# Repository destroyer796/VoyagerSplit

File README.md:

# VoyagerSplit
A wireless low profile keyboard made for [Hack Club](https://hackclub.com/)'s [Blueprint](https://blueprint.hackclub.com/) program. It uses a staggered columnar layout with 28 keys on each side, with 4 thumb buttons. It uses Kailh Choc switches and Seeed Studio Xiao BLE microcontrollers.

## Why?
I decided to design this keyboard to help improve my typing speed and to give me a mechanical keyboard option for when I'm travelling or away from my PC, as I go into college. I wanted to keep it fairly similar to a conventional keyboard though to prevent too much learning curve.

## Renders

## PCB

## Schematic

## BOM
|Item                |Description    |Quantity|Total Price(with shipping)|URL                                                                                                                                                                                                                                                                                                                                                                                                                                                                                                                                                                                                                                                                                                                                                                                 |
|--------------------|---------------|--------|--------------------------|------------------------------------------------------------------------------------------------------------------------------------------------------------------------------------------------------------------------------------------------------------------------------------------------------------------------------------------------------------------------------------------------------------------------------------------------------------------------------------------------------------------------------------------------------------------------------------------------------------------------------------------------------------------------------------------------------------------------------------------------------------------------------------|
|Xiao nRF52840       |Microcontroller|2       |40.06                     |https://www.aliexpress.us/item/3256804273304037.html?spm=a2g0o.productlist.main.17.1d7f5aLD5aLDFO&algo_pvid=72d61333-23ef-4914-a85a-eb0545dd1005&algo_exp_id=72d61333-23ef-4914-a85a-eb0545dd1005-16&pdp_ext_f=%7B%22order%22%3A%22285%22%2C%22eval%22%3A%221%22%2C%22fromPage%22%3A%22search%22%7D&pdp_npi=6%40dis%21USD%2171.90%2153.92%21%21%2171.90%2153.92%21%402101e2b617649016405177918e3363%2112000038983356071%21sea%21US%212965353747%21X%211%210%21n_tag%3A-29919%3Bd%3Add1f422%3Bm03_new_user%3A-29895&curPageLogUid=hr13WqN6qxqv&utparam-url=scene%3Asearch%7Cquery_from%3A%7Cx_object_id%3A1005004459618789%7C_p_origin_prod%3A                                                                                                                                       |
|1N5819 SOD123 Diodes|Diodes         |56      |0.99                      |https://www.aliexpress.us/item/3256801808479789.html?spm=a2g0o.productlist.main.2.5cfb3tgy3tgyW8&algo_pvid=5502a66d-f71d-47d2-b8b7-ee42b102c6e6&algo_exp_id=5502a66d-f71d-47d2-b8b7-ee42b102c6e6-1&pdp_ext_f=%7B%22order%22%3A%22144%22%2C%22eval%22%3A%221%22%2C%22fromPage%22%3A%22search%22%7D&pdp_npi=6%40dis%21USD%211.38%210.99%21%21%211.38%210.99%21%40210337c117649020322812544ee2f6%2112000018351925967%21sea%21US%212965353747%21X%211%210%21n_tag%3A-29919%3Bd%3Add1f422%3Bm03_new_user%3A-29895%3BpisId%3A5000000191712753&curPageLogUid=OMce55HFjq8i&utparam-url=scene%3Asearch%7Cquery_from%3A%7Cx_object_id%3A1005001994794541%7C_p_origin_prod%3A                                                                                                                  |
|Kailh Choc Reds     |Switches       |56      |30.83                     |https://www.aliexpress.us/item/3256808620484354.html?spm=a2g0o.productlist.main.3.39ac194b9vLyR5&algo_pvid=734049b5-ba85-4d7e-95c6-9e496b0393b3&algo_exp_id=734049b5-ba85-4d7e-95c6-9e496b0393b3-2&pdp_ext_f=%7B%22order%22%3A%22189%22%2C%22eval%22%3A%221%22%2C%22fromPage%22%3A%22search%22%7D&pdp_npi=6%40dis%21USD%2130.83%2124.33%21%21%2130.83%2124.33%21%402101e8f317649021499408071e3116%2112000046742202221%21sea%21US%212965353747%21X%211%210%21n_tag%3A-29919%3Bd%3Add1f422%3Bm03_new_user%3A-29895%3BpisId%3A5000000191712753&curPageLogUid=ucF7cwdLXpYV&utparam-url=scene%3Asearch%7Cquery_from%3A%7Cx_object_id%3A1005008806799106%7C_p_origin_prod%3A                                                                                                              |
|Lipo Battery        |140 mAh 302025 |2       |5.51                      |https://www.aliexpress.us/item/3256808031709894.html?spm=a2g0o.productlist.main.4.4571BRfbBRfbo4&aem_p4p_detail=202512041858096342662010559000000555021&algo_pvid=34977370-c03c-490e-b3f1-619f2c1c78e8&algo_exp_id=34977370-c03c-490e-b3f1-619f2c1c78e8-3&pdp_ext_f=%7B%22order%22%3A%222831%22%2C%22eval%22%3A%221%22%2C%22fromPage%22%3A%22search%22%7D&pdp_npi=6%40dis%21USD%2112.25%210.99%21%21%2186.12%216.99%21%40210319b017649034893272527e3fea%2112000044269020516%21sea%21US%212965353747%21X%211%210%21n_tag%3A-29919%3Bd%3Add1f422%3Bm03_new_user%3A-29895%3BpisId%3A5000000191712753&curPageLogUid=PHIdYtYGsZTk&utparam-url=scene%3Asearch%7Cquery_from%3A%7Cx_object_id%3A1005008218024646%7C_p_origin_prod%3A&search_p4p_id=202512041858096342662010559000000555021_1|
|Heatset Inserts     |2x2x3          |10      |2.45                      |https://www.aliexpress.us/item/3256805885174058.html?spm=a2g0o.productlist.main.1.6fae1e486FodJS&algo_pvid=5d92e570-b8b1-4cb0-a5a9-6fed9c97bec5&algo_exp_id=5d92e570-b8b1-4cb0-a5a9-6fed9c97bec5-0&pdp_ext_f=%7B%22order%22%3A%224874%22%2C%22eval%22%3A%221%22%2C%22fromPage%22%3A%22search%22%7D&pdp_npi=6%40dis%21USD%212.12%210.99%21%21%2114.92%216.96%21%402103119c17649895772957789ea3b5%2112000035595774900%21sea%21US%212965353747%21X%211%210%21n_tag%3A-29919%3Bd%3Add1f422%3Bm03_new_user%3A-29895%3BpisId%3A5000000195558357&curPageLogUid=7YsJYdmWdtgS&utparam-url=scene%3Asearch%7Cquery_from%3A%7Cx_object_id%3A1005006071488810%7C_p_origin_prod%3A                                                                                                                |
|Screws              |M2x4           |10      |2.66                      |https://www.aliexpress.us/item/3256809725827194.html?spm=a2g0o.productlist.main.6.3bca51eehZHkh4&algo_pvid=ce5d623b-60fc-463d-b550-49a875e345f0&algo_exp_id=ce5d623b-60fc-463d-b550-49a875e345f0-5&pdp_ext_f=%7B%22order%22%3A%22131%22%2C%22eval%22%3A%221%22%2C%22fromPage%22%3A%22search%22%7D&pdp_npi=6%40dis%21USD%212.56%210.99%21%21%2118.02%216.99%21%402101c59117649925958295120e589f%2112000050558414176%21sea%21US%212965353747%21X%211%210%21n_tag%3A-29919%3Bd%3Add1f422%3Bm03_new_user%3A-29895%3BpisId%3A5000000191712753&curPageLogUid=6hKHBrVGxgKO&utparam-url=scene%3Asearch%7Cquery_from%3A%7Cx_object_id%3A1005009912141946%7C_p_origin_prod%3A                                                                                                                 |

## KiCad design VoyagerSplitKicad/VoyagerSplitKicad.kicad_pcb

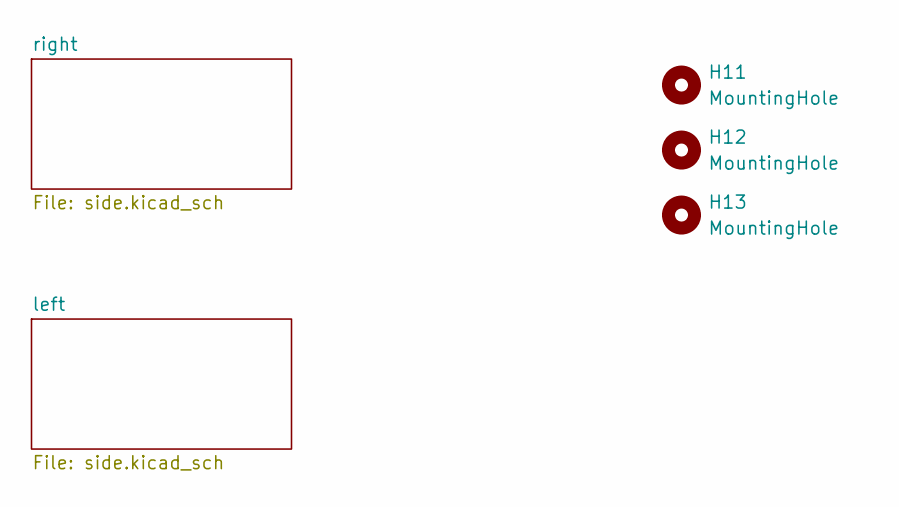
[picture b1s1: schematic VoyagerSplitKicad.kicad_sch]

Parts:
H11, H12, H13: MountingHole; MouseBite-Slot_2.0x4.5mm_outset_D0.5mm_P0.85mm_7h

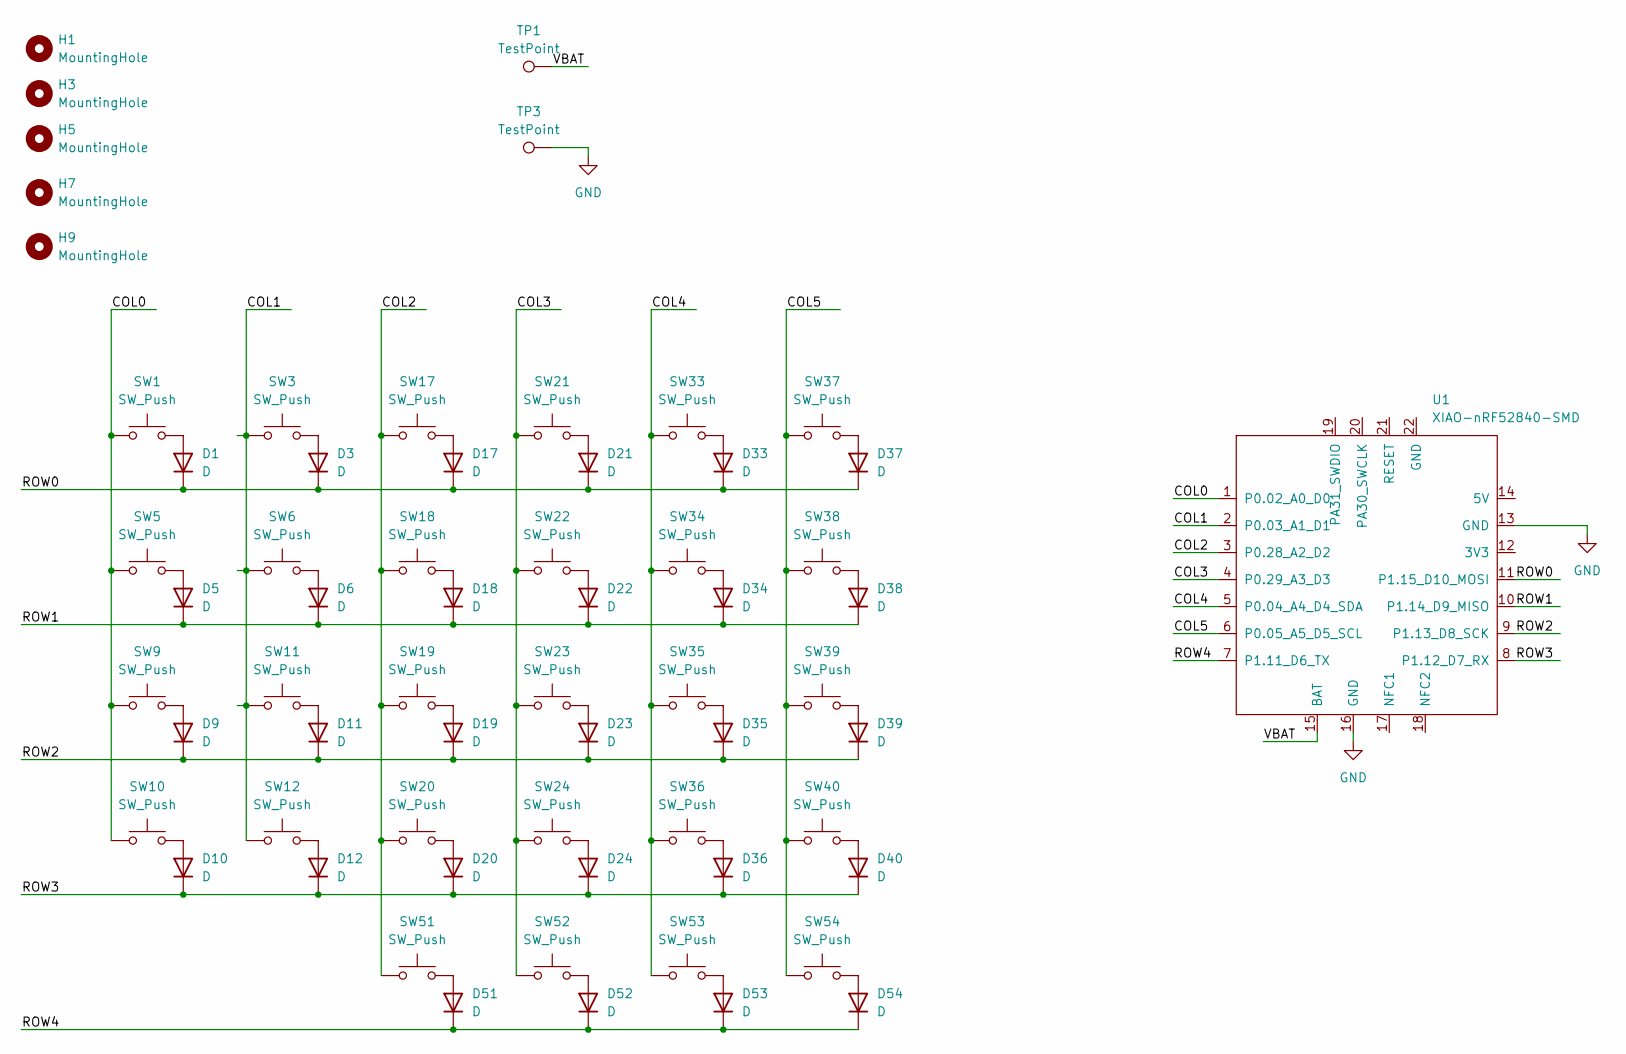
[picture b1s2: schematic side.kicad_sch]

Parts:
D1, D3, D5, D6, D9, D10, D11, D12, D17, D18, D19, D20, D21, D22, D23, D24, D33, D34, D35, D36, D37, D38, D39, D40, D51, D52, D53, D54: D; D_SOD-123
H1, H3, H5, H7, H9: MountingHole; MountingHole_2.2mm_M2
SW1, SW3, SW5, SW6, SW9, SW10, SW11, SW12, SW17, SW18, SW19, SW20, SW21, SW22, SW23, SW24, SW33, SW34, SW35, SW36, SW37, SW38, SW39, SW40, SW51, SW52, SW53, SW54: SW_Push; SW_choc_v1_HS_CPG135001S30_1u
TP1, TP3: TestPoint; TestPoint_Pad_D2.0mm
U1: XIAO-nRF52840-SMD; modified-XIAO-nRF52840-SMD

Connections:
/left/COL0: SW1.1, SW5.1, SW9.1, SW10.1, U1.1 (P0.02_A0_D0)
/left/COL1: SW3.1, SW6.1, SW11.1, SW12.1, U1.2 (P0.03_A1_D1)
/left/COL2: SW17.1, SW18.1, SW19.1, SW20.1, SW51.1, U1.3 (P0.28_A2_D2)
/left/COL3: SW21.1, SW22.1, SW23.1, SW24.1, SW52.1, U1.4 (P0.29_A3_D3)
/left/COL4: SW33.1, SW34.1, SW35.1, SW36.1, SW53.1, U1.5 (P0.04_A4_D4_SDA)
/left/COL5: SW37.1, SW38.1, SW39.1, SW40.1, SW54.1, U1.6 (P0.05_A5_D5_SCL)
/left/ROW0: D1.1 (K), D3.1 (K), D17.1 (K), D21.1 (K), D33.1 (K), D37.1 (K), U1.11 (P1.15_D10_MOSI)
/left/ROW1: D5.1 (K), D6.1 (K), D18.1 (K), D22.1 (K), D34.1 (K), D38.1 (K), U1.10 (P1.14_D9_MISO)
/left/ROW2: D9.1 (K), D11.1 (K), D19.1 (K), D23.1 (K), D35.1 (K), D39.1 (K), U1.9 (P1.13_D8_SCK)
/left/ROW3: D10.1 (K), D12.1 (K), D20.1 (K), D24.1 (K), D36.1 (K), D40.1 (K), U1.8 (P1.12_D7_RX)
/left/ROW4: D51.1 (K), D52.1 (K), D53.1 (K), D54.1 (K), U1.7 (P1.11_D6_TX)
/left/VBAT: U1.15 (BAT); also elsewhere on the board
GND: TP3.1, U1.13 (GND), U1.16 (GND); also elsewhere on the board
unnamed: D1.2 (A), SW1.2
unnamed: D3.2 (A), SW3.2
unnamed: D5.2 (A), SW5.2
unnamed: D6.2 (A), SW6.2
unnamed: D9.2 (A), SW9.2
unnamed: D10.2 (A), SW10.2
unnamed: D11.2 (A), SW11.2
unnamed: D12.2 (A), SW12.2
unnamed: D17.2 (A), SW17.2
unnamed: D18.2 (A), SW18.2
unnamed: D19.2 (A), SW19.2
unnamed: D20.2 (A), SW20.2
unnamed: D21.2 (A), SW21.2
unnamed: D22.2 (A), SW22.2
unnamed: D23.2 (A), SW23.2
unnamed: D24.2 (A), SW24.2
unnamed: D33.2 (A), SW33.2
unnamed: D34.2 (A), SW34.2
unnamed: D35.2 (A), SW35.2
unnamed: D36.2 (A), SW36.2
unnamed: D37.2 (A), SW37.2
unnamed: D38.2 (A), SW38.2
unnamed: D39.2 (A), SW39.2
unnamed: D40.2 (A), SW40.2
unnamed: D51.2 (A), SW51.2
unnamed: D52.2 (A), SW52.2
unnamed: D53.2 (A), SW53.2
unnamed: D54.2 (A), SW54.2

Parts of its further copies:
D2, D4, D7, D8, D13, D14, D15, D16, D25, D26, D27, D28, D29, D30, D31, D32, D41, D42, D43, D44, D45, D46, D47, D48, D57, D58, D59, D60: D; D_SOD-123
H2, H4, H6, H8, H10: MountingHole; MountingHole_2.2mm_M2
SW2, SW4, SW7, SW8, SW13, SW14, SW15, SW16, SW25, SW26, SW27, SW28, SW29, SW30, SW31, SW32, SW41, SW42, SW43, SW44, SW45, SW46, SW47, SW48, SW57, SW58, SW59, SW60: SW_Push; SW_choc_v1_HS_CPG135001S30_1u
U2: XIAO-nRF52840-SMD; modified-XIAO-nRF52840-SMD

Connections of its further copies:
/right/COL0: SW2.1, SW7.1, SW13.1, SW14.1, U2.1 (P0.02_A0_D0)
/right/COL1: SW4.1, SW8.1, SW15.1, SW16.1, U2.2 (P0.03_A1_D1)
/right/COL2: SW25.1, SW26.1, SW27.1, SW28.1, SW57.1, U2.3 (P0.28_A2_D2)
/right/COL3: SW29.1, SW30.1, SW31.1, SW32.1, SW58.1, U2.4 (P0.29_A3_D3)
/right/COL4: SW41.1, SW42.1, SW43.1, SW44.1, SW59.1, U2.5 (P0.04_A4_D4_SDA)
/right/COL5: SW45.1, SW46.1, SW47.1, SW48.1, SW60.1, U2.6 (P0.05_A5_D5_SCL)
/right/ROW0: D2.1 (K), D4.1 (K), D25.1 (K), D29.1 (K), D41.1 (K), D45.1 (K), U2.11 (P1.15_D10_MOSI)
/right/ROW1: D7.1 (K), D8.1 (K), D26.1 (K), D30.1 (K), D42.1 (K), D46.1 (K), U2.10 (P1.14_D9_MISO)
/right/ROW2: D13.1 (K), D15.1 (K), D27.1 (K), D31.1 (K), D43.1 (K), D47.1 (K), U2.9 (P1.13_D8_SCK)
/right/ROW3: D14.1 (K), D16.1 (K), D28.1 (K), D32.1 (K), D44.1 (K), D48.1 (K), U2.8 (P1.12_D7_RX)
/right/ROW4: D57.1 (K), D58.1 (K), D59.1 (K), D60.1 (K), U2.7 (P1.11_D6_TX)
/right/VBAT: U2.15 (BAT); also elsewhere on the board
GND: U2.13 (GND), U2.16 (GND); also elsewhere on the board
unnamed: D2.2 (A), SW2.2
unnamed: D4.2 (A), SW4.2
unnamed: D7.2 (A), SW7.2
unnamed: D8.2 (A), SW8.2
unnamed: D13.2 (A), SW13.2
unnamed: D14.2 (A), SW14.2
unnamed: D15.2 (A), SW15.2
unnamed: D16.2 (A), SW16.2
unnamed: D25.2 (A), SW25.2
unnamed: D26.2 (A), SW26.2
unnamed: D27.2 (A), SW27.2
unnamed: D28.2 (A), SW28.2
unnamed: D29.2 (A), SW29.2
unnamed: D30.2 (A), SW30.2
unnamed: D31.2 (A), SW31.2
unnamed: D32.2 (A), SW32.2
unnamed: D41.2 (A), SW41.2
unnamed: D42.2 (A), SW42.2
unnamed: D43.2 (A), SW43.2
unnamed: D44.2 (A), SW44.2
unnamed: D45.2 (A), SW45.2
unnamed: D46.2 (A), SW46.2
unnamed: D47.2 (A), SW47.2
unnamed: D48.2 (A), SW48.2
unnamed: D57.2 (A), SW57.2
unnamed: D58.2 (A), SW58.2
unnamed: D59.2 (A), SW59.2
unnamed: D60.2 (A), SW60.2

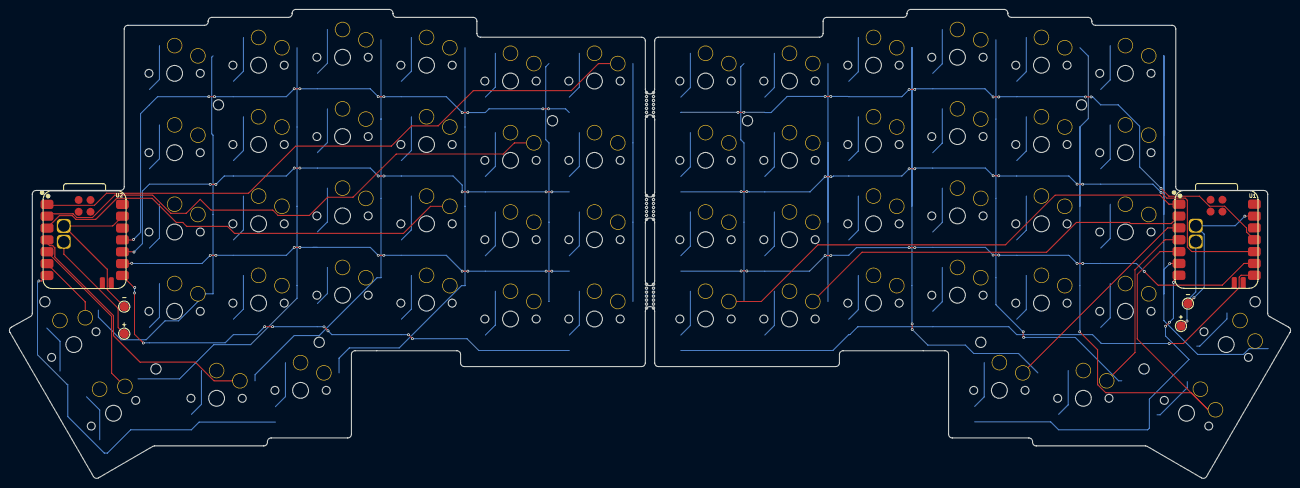
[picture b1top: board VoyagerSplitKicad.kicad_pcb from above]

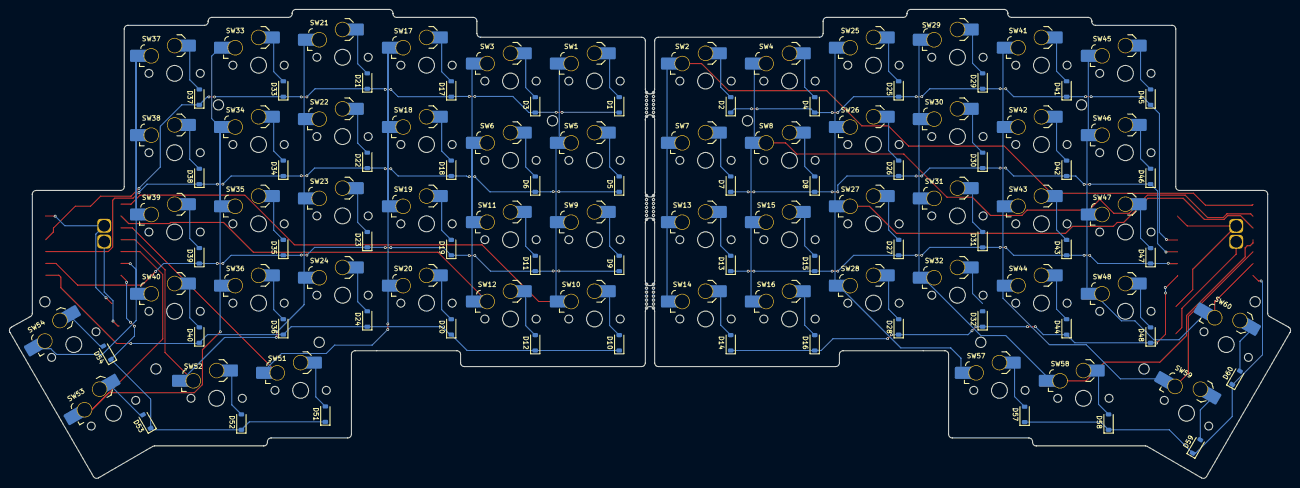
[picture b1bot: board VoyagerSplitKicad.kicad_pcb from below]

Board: 2 copper layers, 274.6 x 100.5 mm, 131 parts (112 on the bottom side), 81 nets.

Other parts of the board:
+: TestPoint; TestPoint_Pad_D2.0mm
+#2: TestPoint; TestPoint_Pad_D2.0mm
-: TestPoint; TestPoint_Pad_D2.0mm
-#2: TestPoint; TestPoint_Pad_D2.0mm

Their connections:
/left/VBAT: +#2.1; also elsewhere on the board
/right/VBAT: +.1; also elsewhere on the board
GND: -.1, -#2.1; also elsewhere on the board

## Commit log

2025-11-24 kicad schematic
2025-11-24 journal image and new symbol location
2025-11-25 layed out one half of pcb
2025-11-27 laying out 2nd half of PCB and getting edge cut
2025-12-04 added 3d
2025-12-05 flipped xiao
2025-12-06 CAD!
2025-12-06 added fusion file
2026-03-31 recipts
2026-04-01 soldered half!
2026-04-04 4-3pics
2026-04-07 updated cad
